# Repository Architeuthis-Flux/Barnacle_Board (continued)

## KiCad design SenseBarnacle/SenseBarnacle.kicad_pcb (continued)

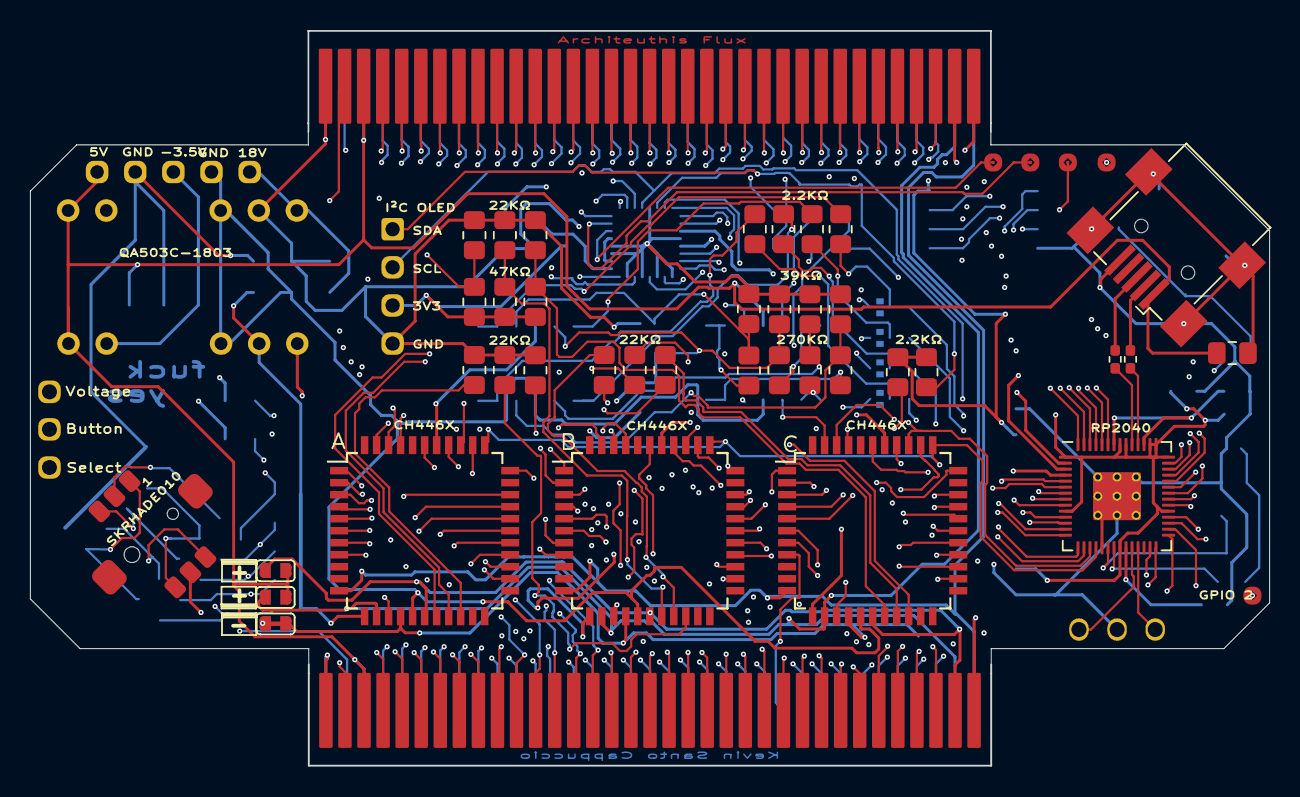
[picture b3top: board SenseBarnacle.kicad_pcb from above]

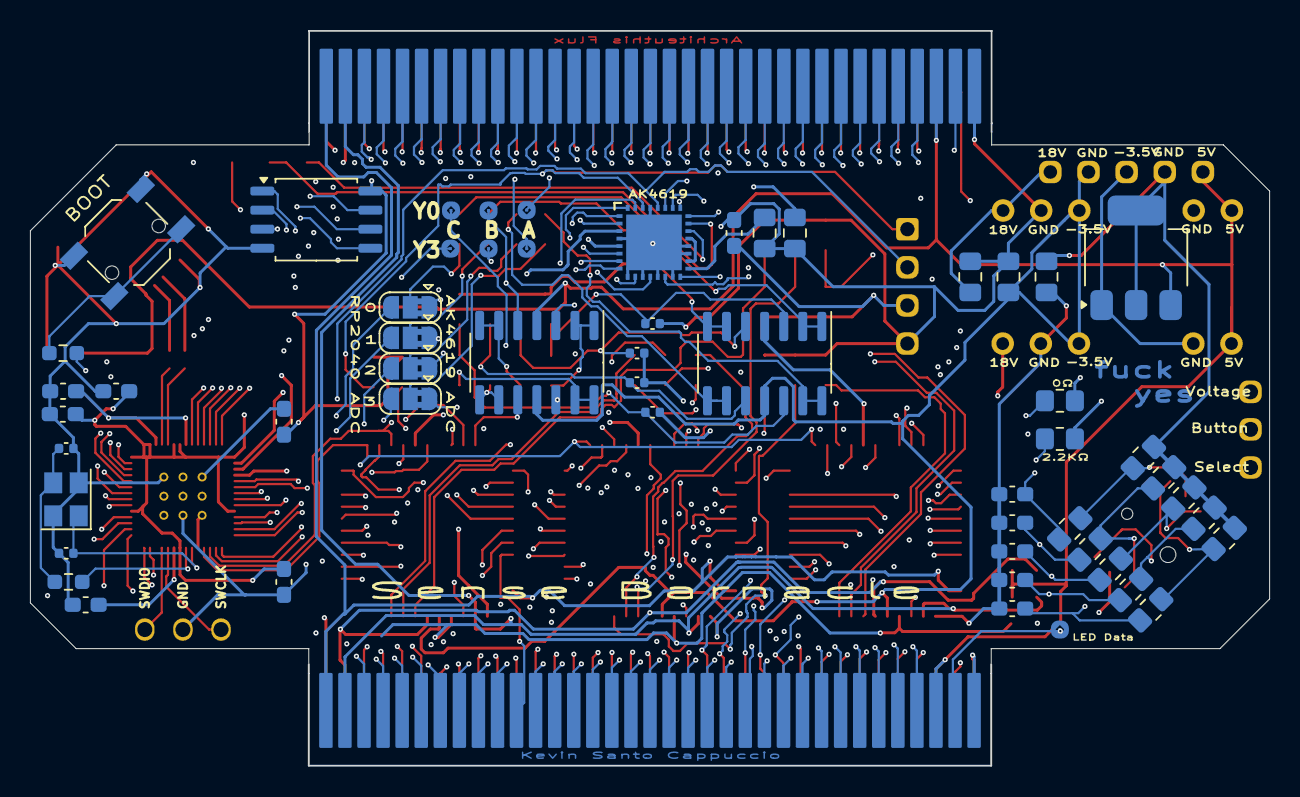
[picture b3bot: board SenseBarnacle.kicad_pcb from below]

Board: 4 copper layers, 82.6 x 48.9 mm, 108 parts (57 on the bottom side), 167 nets.

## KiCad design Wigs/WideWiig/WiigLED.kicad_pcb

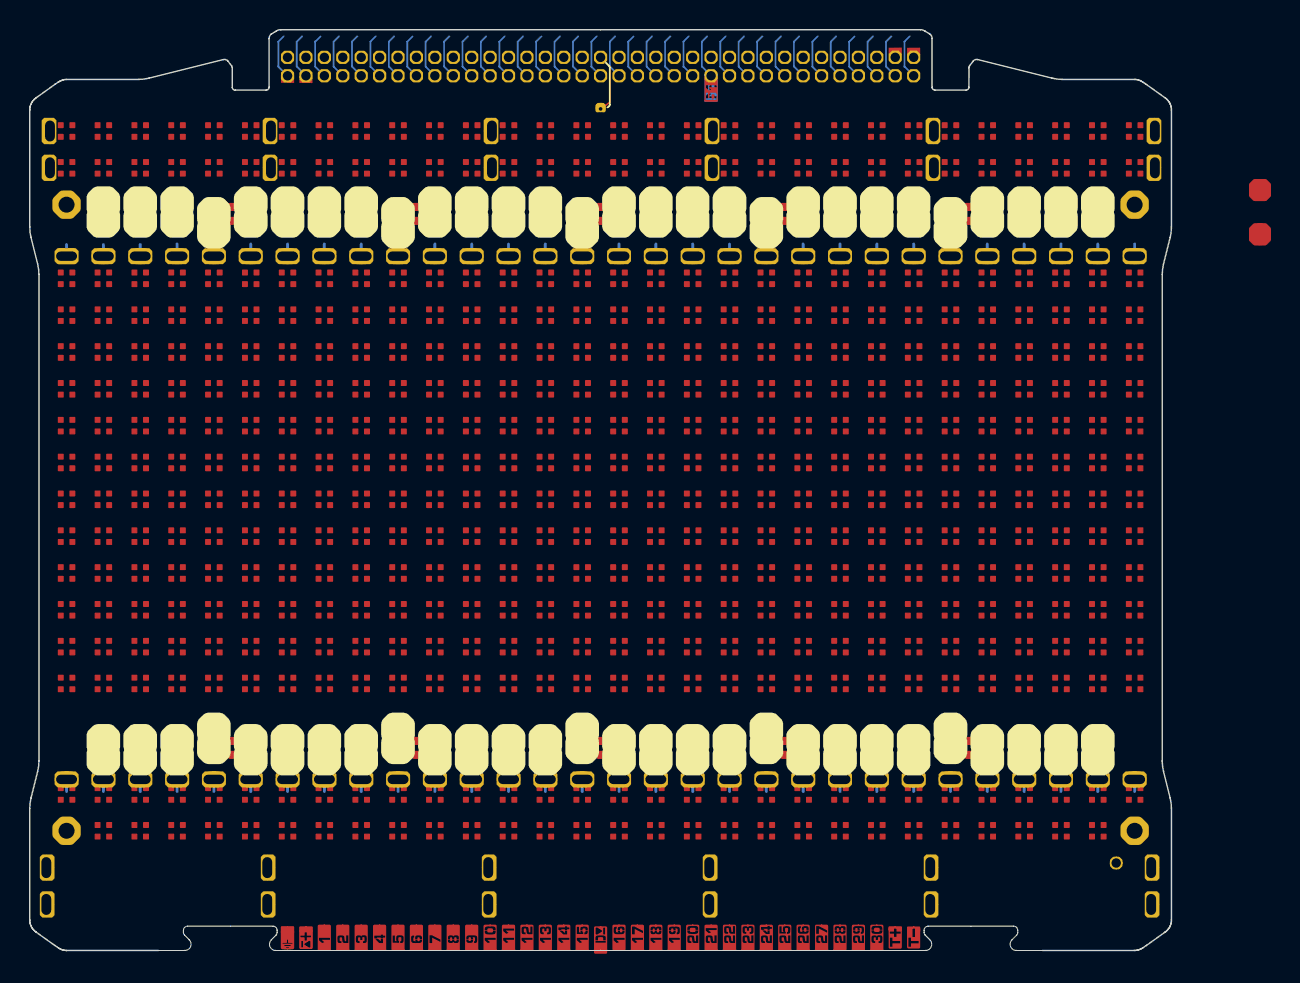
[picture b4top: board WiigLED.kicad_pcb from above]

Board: 4 copper layers, 78.7 x 63.5 mm, 505 parts (0 on the bottom side), 552 nets, no tracks yet.

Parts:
C1, C2, C3, C4, C5, C6, C7, C8, C9, C10, C11, C12, C13, C14: 1uF; C_0402_1005Metric
D11, D12, D13, D14, D15, D16, D21, D22, D23, D24, D25, D26, D31, D32, D33, D34, D35, D36, D41, D42, D43, D44, D45, D46, D51, D52, D53, D54, D55, D56, D61, D62, D63, D64, D65, D66, D71, D72, D73, D74, D75, D76, D81, D82, D83, D84, D85, D86, D91, D92, D93, D94, D95, D96, D101, D102, D103, D104, D105, D106, D111, D112, D113, D114, D115, D116, D121, D122, D123, D124, D125, D126, D131, D132, D133, D134, D135, D136, D141, D142, D143, D144, D145, D146, D151, D152, D153, D154, D155, D156, D161, D162, D163, D164, D165, D166, D171, D172, D173, D174, D175, D176, D181, D182, D183, D184, D185, D186, D191, D192, D193, D194, D195, D196, D201, D202, D203, D204, D205, D206, D211, D212, D213, D214, D215, D216, D221, D222, D223, D224, D225, D226, D231, D232, D233, D234, D235, D236, D241, D242, D243, D244, D245, D246, D251, D252, D253, D254, D255, D256, D261, D262, D263, D264, D265, D266, D271, D272, D273, D274, D275, D276, D281, D282, D283, D284, D285, D286, D291, D292, D293, D294, D295, D296, D301, D302, D303, D304, D305, D306, D311, D312, D313, D314, D315, D316, D321, D322, D323, D324, D325, D326, D331, D332, D333, D334, D335, D336, D341, D342, D343, D344, D345, D346, D351, D352, D353, D354, D355, D356, D361, D362, D363, D364, D365, D366, D371, D372, D373, D374, D375, D376, D381, D382, D383, D384, D385, D386, D391, D392, D393, D394, D395, D396, D401, D402, D403, D404, D405, D406, D411, D412, D413, D414, D415, D416, D421, D422, D423, D424, D425, D426, D431, D432, D433, D434, D435, D436, D441, D442, D443, D444, D445, D446, D451, D452, D453, D454, D455, D456, D461, D462, D463, D464, D465, D466, D471, D472, D473, D474, D475, D476, D481, D482, D483, D484, D485, D486, D491, D492, D493, D494, D495, D496, D501, D502, D503, D504, D505, D506, D511, D512, D513, D514, D515, D516, D521, D522, D523, D524, D525, D526, D531, D532, D533, D534, D535, D536, D541, D542, D543, D544, D545, D546, D551, D552, D553, D554, D555, D556, D561, D562, D563, D564, D565, D566, D571, D572, D573, D574, D575, D576, D581, D582, D583, D584, D585, D586, D591, D592, D593, D594, D595, D596, D601, D602, D603, D604, D605, D606, D611, D612, D613, D614, D615, D616, D617, D618, D619, D621, D622, D623, D624, D625, D626, D627, D628, D629, D631, D632, D633, D634, D635, D636, D637, D638, D639, D641, D642, D643, D644, D645, D646, D647, D648, D649, D6110, D6111, D6112, D6113, D6114, D6115, D6116, D6117, D6118, D6119, D6120, D6121, D6122, D6123, D6124, D6125, D6126, D6127, D6128, D6129, D6130, D6210, D6211, D6212, D6213, D6214, D6215, D6216, D6217, D6218, D6219, D6220, D6221, D6222, D6223, D6224, D6225, D6226, D6227, D6228, D6229, D6230, D6310, D6311, D6312, D6313, D6314, D6315, D6316, D6317, D6318, D6319, D6320, D6321, D6322, D6323, D6324, D6325, D6326, D6327, D6328, D6329, D6330, D6410, D6411, D6412, D6413, D6414, D6415, D6416, D6417, D6418, D6419, D6420, D6421, D6422, D6423, D6424, D6425, D6426, D6427, D6428, D6429, D6430: WS2812B; WS2812B-1313
J1: SENSE_60; Conn_1x1_SenseRiser
J1#2: SENSE_60; HEE70LP03BK_NumberedPads_CardGuide
J2: Barnacle_Connector_70pin; PinHeader_2x35_P1.27_wiig_card
J3: Barnacle_Connector_70pin; SideConnect_sparserrr_Bottom_tighter
J4: SENSE_1; Conn_1x1_SenseRiser
J5: SENSE_30; Conn_1x1_SenseRiser
J6: SENSE_31; Conn_1x1_SenseRiser
J11: Breadboard_6NonHoles
TP1, TP2: GND; TestPoint_Pad_D1.0mm
TP3: LED OUT; PinHeader_1x1_0.6mm_tinyAF

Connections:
+5V: C1.1, C2.1, C3.1, C4.1, C5.1, C6.1, C7.1, C8.1, C9.1, C10.1, C11.1, C12.1, C13.1, C14.1, D11.2 (VDD), D12.2 (VDD), D13.2 (VDD), D14.2 (VDD), D15.2 (VDD), D16.2 (VDD), D21.2 (VDD), D22.2 (VDD), D23.2 (VDD), D24.2 (VDD), D25.2 (VDD), D26.2 (VDD), D31.2 (VDD), D32.2 (VDD), D33.2 (VDD), D34.2 (VDD), D35.2 (VDD), D36.2 (VDD), D41.2 (VDD), D42.2 (VDD), D43.2 (VDD), D44.2 (VDD), D45.2 (VDD), D46.2 (VDD), D51.2 (VDD), D52.2 (VDD), D53.2 (VDD), D54.2 (VDD), D55.2 (VDD), D56.2 (VDD), D61.2 (VDD), D62.2 (VDD), D63.2 (VDD), D64.2 (VDD), D65.2 (VDD), D66.2 (VDD), D71.2 (VDD), D72.2 (VDD), D73.2 (VDD), D74.2 (VDD), D75.2 (VDD), D76.2 (VDD), D81.2 (VDD), D82.2 (VDD), D83.2 (VDD), D84.2 (VDD), D85.2 (VDD), D86.2 (VDD), D91.2 (VDD), D92.2 (VDD), D93.2 (VDD), D94.2 (VDD), D95.2 (VDD), D96.2 (VDD), D101.2 (VDD), D102.2 (VDD), D103.2 (VDD), D104.2 (VDD), D105.2 (VDD), D106.2 (VDD), D111.2 (VDD), D112.2 (VDD), D113.2 (VDD), D114.2 (VDD), D115.2 (VDD), D116.2 (VDD), D121.2 (VDD), D122.2 (VDD), D123.2 (VDD), D124.2 (VDD), D125.2 (VDD), D126.2 (VDD), D131.2 (VDD), D132.2 (VDD), D133.2 (VDD), D134.2 (VDD), D135.2 (VDD), D136.2 (VDD), D141.2 (VDD), D142.2 (VDD), D143.2 (VDD), D144.2 (VDD), D145.2 (VDD), D146.2 (VDD), D151.2 (VDD), D152.2 (VDD), D153.2 (VDD), D154.2 (VDD), D155.2 (VDD), D156.2 (VDD), D161.2 (VDD), D162.2 (VDD), D163.2 (VDD), D164.2 (VDD), D165.2 (VDD), D166.2 (VDD), D171.2 (VDD), D172.2 (VDD), D173.2 (VDD), D174.2 (VDD), D175.2 (VDD), D176.2 (VDD), D181.2 (VDD), D182.2 (VDD), D183.2 (VDD), D184.2 (VDD), D185.2 (VDD), D186.2 (VDD), D191.2 (VDD), D192.2 (VDD), D193.2 (VDD), D194.2 (VDD), D195.2 (VDD), D196.2 (VDD), D201.2 (VDD), D202.2 (VDD), D203.2 (VDD), D204.2 (VDD), D205.2 (VDD), D206.2 (VDD), D211.2 (VDD), D212.2 (VDD), D213.2 (VDD), D214.2 (VDD), D215.2 (VDD), D216.2 (VDD), D221.2 (VDD), D222.2 (VDD), D223.2 (VDD), D224.2 (VDD), D225.2 (VDD), D226.2 (VDD), D231.2 (VDD), D232.2 (VDD), D233.2 (VDD), D234.2 (VDD), D235.2 (VDD), D236.2 (VDD), D241.2 (VDD), D242.2 (VDD), D243.2 (VDD), D244.2 (VDD), D245.2 (VDD), D246.2 (VDD), D251.2 (VDD), D252.2 (VDD), D253.2 (VDD), D254.2 (VDD), D255.2 (VDD), D256.2 (VDD), D261.2 (VDD), D262.2 (VDD), D263.2 (VDD), D264.2 (VDD), D265.2 (VDD), D266.2 (VDD), D271.2 (VDD), D272.2 (VDD), D273.2 (VDD), D274.2 (VDD), D275.2 (VDD), D276.2 (VDD), D281.2 (VDD), D282.2 (VDD), D283.2 (VDD), D284.2 (VDD), D285.2 (VDD), D286.2 (VDD), D291.2 (VDD), D292.2 (VDD), D293.2 (VDD), D294.2 (VDD), D295.2 (VDD), D296.2 (VDD), D301.2 (VDD), D302.2 (VDD), D303.2 (VDD), D304.2 (VDD), D305.2 (VDD), D306.2 (VDD), D311.2 (VDD), D312.2 (VDD), D313.2 (VDD), D314.2 (VDD), D315.2 (VDD), D316.2 (VDD), D321.2 (VDD), D322.2 (VDD), D323.2 (VDD), D324.2 (VDD), D325.2 (VDD), D326.2 (VDD), D331.2 (VDD), D332.2 (VDD), D333.2 (VDD), D334.2 (VDD), D335.2 (VDD), D336.2 (VDD), D341.2 (VDD), D342.2 (VDD), D343.2 (VDD), D344.2 (VDD), D345.2 (VDD), D346.2 (VDD), D351.2 (VDD), D352.2 (VDD), D353.2 (VDD), D354.2 (VDD), D355.2 (VDD), D356.2 (VDD), D361.2 (VDD), D362.2 (VDD), D363.2 (VDD), D364.2 (VDD), D365.2 (VDD), D366.2 (VDD), D371.2 (VDD), D372.2 (VDD), D373.2 (VDD), D374.2 (VDD), D375.2 (VDD), D376.2 (VDD), D381.2 (VDD), D382.2 (VDD), D383.2 (VDD), D384.2 (VDD), D385.2 (VDD), D386.2 (VDD), D391.2 (VDD), D392.2 (VDD), D393.2 (VDD), D394.2 (VDD), D395.2 (VDD), D396.2 (VDD), D401.2 (VDD), D402.2 (VDD), D403.2 (VDD), D404.2 (VDD), D405.2 (VDD), D406.2 (VDD), D411.2 (VDD), D412.2 (VDD), D413.2 (VDD), D414.2 (VDD), D415.2 (VDD), D416.2 (VDD), D421.2 (VDD), D422.2 (VDD), D423.2 (VDD), D424.2 (VDD), D425.2 (VDD), D426.2 (VDD), D431.2 (VDD), D432.2 (VDD), D433.2 (VDD), D434.2 (VDD), D435.2 (VDD), D436.2 (VDD), D441.2 (VDD), D442.2 (VDD), D443.2 (VDD), D444.2 (VDD), D445.2 (VDD), D446.2 (VDD), D451.2 (VDD), D452.2 (VDD), D453.2 (VDD), D454.2 (VDD), D455.2 (VDD), D456.2 (VDD), D461.2 (VDD), D462.2 (VDD), D463.2 (VDD), D464.2 (VDD), D465.2 (VDD), D466.2 (VDD), D471.2 (VDD), D472.2 (VDD), D473.2 (VDD), D474.2 (VDD), D475.2 (VDD), D476.2 (VDD), D481.2 (VDD), D482.2 (VDD), D483.2 (VDD), D484.2 (VDD), D485.2 (VDD), D486.2 (VDD), D491.2 (VDD), D492.2 (VDD), D493.2 (VDD), D494.2 (VDD), D495.2 (VDD), D496.2 (VDD), D501.2 (VDD), D502.2 (VDD), D503.2 (VDD), D504.2 (VDD), D505.2 (VDD), D506.2 (VDD), D511.2 (VDD), D512.2 (VDD), D513.2 (VDD), D514.2 (VDD), D515.2 (VDD), D516.2 (VDD), D521.2 (VDD), D522.2 (VDD), D523.2 (VDD), D524.2 (VDD), D525.2 (VDD), D526.2 (VDD), D531.2 (VDD), D532.2 (VDD), D533.2 (VDD), D534.2 (VDD), D535.2 (VDD), D536.2 (VDD), D541.2 (VDD), D542.2 (VDD), D543.2 (VDD), D544.2 (VDD), D545.2 (VDD), D546.2 (VDD), D551.2 (VDD), D552.2 (VDD), D553.2 (VDD), D554.2 (VDD), D555.2 (VDD), D556.2 (VDD), D561.2 (VDD), D562.2 (VDD), D563.2 (VDD), D564.2 (VDD), D565.2 (VDD), D566.2 (VDD), D571.2 (VDD), D572.2 (VDD), D573.2 (VDD), D574.2 (VDD), D575.2 (VDD), D576.2 (VDD), D581.2 (VDD), D582.2 (VDD), D583.2 (VDD), D584.2 (VDD), D585.2 (VDD), D586.2 (VDD), D591.2 (VDD), D592.2 (VDD), D593.2 (VDD), D594.2 (VDD), D595.2 (VDD), D596.2 (VDD), D601.2 (VDD), D602.2 (VDD), D603.2 (VDD), D604.2 (VDD), D605.2 (VDD), D606.2 (VDD), D611.2 (VDD), D612.2 (VDD), D613.2 (VDD), D614.2 (VDD), D615.2 (VDD), D616.2 (VDD), D617.2 (VDD), D618.2 (VDD), D619.2 (VDD), D621.2 (VDD), D622.2 (VDD), D623.2 (VDD), D624.2 (VDD), D625.2 (VDD), D626.2 (VDD), D627.2 (VDD), D628.2 (VDD), D629.2 (VDD), D631.2 (VDD), D632.2 (VDD), D633.2 (VDD), D634.2 (VDD), D635.2 (VDD), D636.2 (VDD), D637.2 (VDD), D638.2 (VDD), D639.2 (VDD), D641.2 (VDD), D642.2 (VDD), D643.2 (VDD), D644.2 (VDD), D645.2 (VDD), D646.2 (VDD), D647.2 (VDD), D648.2 (VDD), D649.2 (VDD), D6110.2 (VDD), D6111.2 (VDD), D6112.2 (VDD), D6113.2 (VDD), D6114.2 (VDD), D6115.2 (VDD), D6116.2 (VDD), D6117.2 (VDD), D6118.2 (VDD), D6119.2 (VDD), D6120.2 (VDD), D6121.2 (VDD), D6122.2 (VDD), D6123.2 (VDD), D6124.2 (VDD), D6125.2 (VDD), D6126.2 (VDD), D6127.2 (VDD), D6128.2 (VDD), D6129.2 (VDD), D6130.2 (VDD), D6210.2 (VDD), D6211.2 (VDD), D6212.2 (VDD), D6213.2 (VDD), D6214.2 (VDD), D6215.2 (VDD), D6216.2 (VDD), D6217.2 (VDD), D6218.2 (VDD), D6219.2 (VDD), D6220.2 (VDD), D6221.2 (VDD), D6222.2 (VDD), D6223.2 (VDD), D6224.2 (VDD), D6225.2 (VDD), D6226.2 (VDD), D6227.2 (VDD), D6228.2 (VDD), D6229.2 (VDD), D6230.2 (VDD), D6310.2 (VDD), D6311.2 (VDD), D6312.2 (VDD), D6313.2 (VDD), D6314.2 (VDD), D6315.2 (VDD), D6316.2 (VDD), D6317.2 (VDD), D6318.2 (VDD), D6319.2 (VDD), D6320.2 (VDD), D6321.2 (VDD), D6322.2 (VDD), D6323.2 (VDD), D6324.2 (VDD), D6325.2 (VDD), D6326.2 (VDD), D6327.2 (VDD), D6328.2 (VDD), D6329.2 (VDD), D6330.2 (VDD), D6410.2 (VDD), D6411.2 (VDD), D6412.2 (VDD), D6413.2 (VDD), D6414.2 (VDD), D6415.2 (VDD), D6416.2 (VDD), D6417.2 (VDD), D6418.2 (VDD), D6419.2 (VDD), D6420.2 (VDD), D6421.2 (VDD), D6422.2 (VDD), D6423.2 (VDD), D6424.2 (VDD), D6425.2 (VDD), D6426.2 (VDD), D6427.2 (VDD), D6428.2 (VDD), D6429.2 (VDD)
GND: C1.2, C2.2, C3.2, C4.2, C5.2, C6.2, C7.2, C8.2, C9.2, C10.2, C11.2, C12.2, C13.2, C14.2, D11.3 (VSS), D12.3 (VSS), D13.3 (VSS), D14.3 (VSS), D15.3 (VSS), D16.3 (VSS), D21.3 (VSS), D22.3 (VSS), D23.3 (VSS), D24.3 (VSS), D25.3 (VSS), D26.3 (VSS), D31.3 (VSS), D32.3 (VSS), D33.3 (VSS), D34.3 (VSS), D35.3 (VSS), D36.3 (VSS), D41.3 (VSS), D42.3 (VSS), D43.3 (VSS), D44.3 (VSS), D45.3 (VSS), D46.3 (VSS), D51.3 (VSS), D52.3 (VSS), D53.3 (VSS), D54.3 (VSS), D55.3 (VSS), D56.3 (VSS), D61.3 (VSS), D62.3 (VSS), D63.3 (VSS), D64.3 (VSS), D65.3 (VSS), D66.3 (VSS), D71.3 (VSS), D72.3 (VSS), D73.3 (VSS), D74.3 (VSS), D75.3 (VSS), D76.3 (VSS), D81.3 (VSS), D82.3 (VSS), D83.3 (VSS), D84.3 (VSS), D85.3 (VSS), D86.3 (VSS), D91.3 (VSS), D92.3 (VSS), D93.3 (VSS), D94.3 (VSS), D95.3 (VSS), D96.3 (VSS), D101.3 (VSS), D102.3 (VSS), D103.3 (VSS), D104.3 (VSS), D105.3 (VSS), D106.3 (VSS), D111.3 (VSS), D112.3 (VSS), D113.3 (VSS), D114.3 (VSS), D115.3 (VSS), D116.3 (VSS), D121.3 (VSS), D122.3 (VSS), D123.3 (VSS), D124.3 (VSS), D125.3 (VSS), D126.3 (VSS), D131.3 (VSS), D132.3 (VSS), D133.3 (VSS), D134.3 (VSS), D135.3 (VSS), D136.3 (VSS), D141.3 (VSS), D142.3 (VSS), D143.3 (VSS), D144.3 (VSS), D145.3 (VSS), D146.3 (VSS), D151.3 (VSS), D152.3 (VSS), D153.3 (VSS), D154.3 (VSS), D155.3 (VSS), D156.3 (VSS), D161.3 (VSS), D162.3 (VSS), D163.3 (VSS), D164.3 (VSS), D165.3 (VSS), D166.3 (VSS), D171.3 (VSS), D172.3 (VSS), D173.3 (VSS), D174.3 (VSS), D175.3 (VSS), D176.3 (VSS), D181.3 (VSS), D182.3 (VSS), D183.3 (VSS), D184.3 (VSS), D185.3 (VSS), D186.3 (VSS), D191.3 (VSS), D192.3 (VSS), D193.3 (VSS), D194.3 (VSS), D195.3 (VSS), D196.3 (VSS), D201.3 (VSS), D202.3 (VSS), D203.3 (VSS), D204.3 (VSS), D205.3 (VSS), D206.3 (VSS), D211.3 (VSS), D212.3 (VSS), D213.3 (VSS), D214.3 (VSS), D215.3 (VSS), D216.3 (VSS), D221.3 (VSS), D222.3 (VSS), D223.3 (VSS), D224.3 (VSS), D225.3 (VSS), D226.3 (VSS), D231.3 (VSS), D232.3 (VSS), D233.3 (VSS), D234.3 (VSS), D235.3 (VSS), D236.3 (VSS), D241.3 (VSS), D242.3 (VSS), D243.3 (VSS), D244.3 (VSS), D245.3 (VSS), D246.3 (VSS), D251.3 (VSS), D252.3 (VSS), D253.3 (VSS), D254.3 (VSS), D255.3 (VSS), D256.3 (VSS), D261.3 (VSS), D262.3 (VSS), D263.3 (VSS), D264.3 (VSS), D265.3 (VSS), D266.3 (VSS), D271.3 (VSS), D272.3 (VSS), D273.3 (VSS), D274.3 (VSS), D275.3 (VSS), D276.3 (VSS), D281.3 (VSS), D282.3 (VSS), D283.3 (VSS), D284.3 (VSS), D285.3 (VSS), D286.3 (VSS), D291.3 (VSS), D292.3 (VSS), D293.3 (VSS), D294.3 (VSS), D295.3 (VSS), D296.3 (VSS), D301.3 (VSS), D302.3 (VSS), D303.3 (VSS), D304.3 (VSS), D305.3 (VSS), D306.3 (VSS), D311.3 (VSS), D312.3 (VSS), D313.3 (VSS), D314.3 (VSS), D315.3 (VSS), D316.3 (VSS), D321.3 (VSS), D322.3 (VSS), D323.3 (VSS), D324.3 (VSS), D325.3 (VSS), D326.3 (VSS), D331.3 (VSS), D332.3 (VSS), D333.3 (VSS), D334.3 (VSS), D335.3 (VSS), D336.3 (VSS), D341.3 (VSS), D342.3 (VSS), D343.3 (VSS), D344.3 (VSS), D345.3 (VSS), D346.3 (VSS), D351.3 (VSS), D352.3 (VSS), D353.3 (VSS), D354.3 (VSS), D355.3 (VSS), D356.3 (VSS), D361.3 (VSS), D362.3 (VSS), D363.3 (VSS), D364.3 (VSS), D365.3 (VSS), D366.3 (VSS), D371.3 (VSS), D372.3 (VSS), D373.3 (VSS), D374.3 (VSS), D375.3 (VSS), D376.3 (VSS), D381.3 (VSS), D382.3 (VSS), D383.3 (VSS), D384.3 (VSS), D385.3 (VSS), D386.3 (VSS), D391.3 (VSS), D392.3 (VSS), D393.3 (VSS), D394.3 (VSS), D395.3 (VSS), D396.3 (VSS), D401.3 (VSS), D402.3 (VSS), D403.3 (VSS), D404.3 (VSS), D405.3 (VSS), D406.3 (VSS), D411.3 (VSS), D412.3 (VSS), D413.3 (VSS), D414.3 (VSS), D415.3 (VSS), D416.3 (VSS), D421.3 (VSS), D422.3 (VSS), D423.3 (VSS), D424.3 (VSS), D425.3 (VSS), D426.3 (VSS), D431.3 (VSS), D432.3 (VSS), D433.3 (VSS), D434.3 (VSS), D435.3 (VSS), D436.3 (VSS), D441.3 (VSS), D442.3 (VSS), D443.3 (VSS), D444.3 (VSS), D445.3 (VSS), D446.3 (VSS), D451.3 (VSS), D452.3 (VSS), D453.3 (VSS), D454.3 (VSS), D455.3 (VSS), D456.3 (VSS), D461.3 (VSS), D462.3 (VSS), D463.3 (VSS), D464.3 (VSS), D465.3 (VSS), D466.3 (VSS), D471.3 (VSS), D472.3 (VSS), D473.3 (VSS), D474.3 (VSS), D475.3 (VSS), D476.3 (VSS), D481.3 (VSS), D482.3 (VSS), D483.3 (VSS), D484.3 (VSS), D485.3 (VSS), D486.3 (VSS), D491.3 (VSS), D492.3 (VSS), D493.3 (VSS), D494.3 (VSS), D495.3 (VSS), D496.3 (VSS), D501.3 (VSS), D502.3 (VSS), D503.3 (VSS), D504.3 (VSS), D505.3 (VSS), D506.3 (VSS), D511.3 (VSS), D512.3 (VSS), D513.3 (VSS), D514.3 (VSS), D515.3 (VSS), D516.3 (VSS), D521.3 (VSS), D522.3 (VSS), D523.3 (VSS), D524.3 (VSS), D525.3 (VSS), D526.3 (VSS), D531.3 (VSS), D532.3 (VSS), D533.3 (VSS), D534.3 (VSS), D535.3 (VSS), D536.3 (VSS), D541.3 (VSS), D542.3 (VSS), D543.3 (VSS), D544.3 (VSS), D545.3 (VSS), D546.3 (VSS), D551.3 (VSS), D552.3 (VSS), D553.3 (VSS), D554.3 (VSS), D555.3 (VSS), D556.3 (VSS), D561.3 (VSS), D562.3 (VSS), D563.3 (VSS), D564.3 (VSS), D565.3 (VSS), D566.3 (VSS), D571.3 (VSS), D572.3 (VSS), D573.3 (VSS), D574.3 (VSS), D575.3 (VSS), D576.3 (VSS), D581.3 (VSS), D582.3 (VSS), D583.3 (VSS), D584.3 (VSS), D585.3 (VSS), D586.3 (VSS), D591.3 (VSS), D592.3 (VSS), D593.3 (VSS), D594.3 (VSS), D595.3 (VSS), D596.3 (VSS), D601.3 (VSS), D602.3 (VSS), D603.3 (VSS), D604.3 (VSS), D605.3 (VSS), D606.3 (VSS), D611.3 (VSS), D612.3 (VSS), D613.3 (VSS), D614.3 (VSS), D615.3 (VSS), D616.3 (VSS), D617.3 (VSS), D618.3 (VSS), D619.3 (VSS), D621.3 (VSS), D622.3 (VSS), D623.3 (VSS), D624.3 (VSS), D625.3 (VSS), D626.3 (VSS), D627.3 (VSS), D628.3 (VSS), D629.3 (VSS), D631.3 (VSS), D632.3 (VSS), D633.3 (VSS), D634.3 (VSS), D635.3 (VSS), D636.3 (VSS), D637.3 (VSS), D638.3 (VSS), D639.3 (VSS), D641.3 (VSS), D642.3 (VSS), D643.3 (VSS), D644.3 (VSS), D645.3 (VSS), D646.3 (VSS), D647.3 (VSS), D648.3 (VSS), D649.3 (VSS), D6110.3 (VSS), D6111.3 (VSS), D6112.3 (VSS), D6113.3 (VSS), D6114.3 (VSS), D6115.3 (VSS), D6116.3 (VSS), D6117.3 (VSS), D6118.3 (VSS), D6119.3 (VSS), D6120.3 (VSS), D6121.3 (VSS), D6122.3 (VSS), D6123.3 (VSS), D6124.3 (VSS), D6125.3 (VSS), D6126.3 (VSS), D6127.3 (VSS), D6128.3 (VSS), D6129.3 (VSS), D6130.3 (VSS), D6210.3 (VSS), D6211.3 (VSS), D6212.3 (VSS), D6213.3 (VSS), D6214.3 (VSS), D6215.3 (VSS), D6216.3 (VSS), D6217.3 (VSS), D6218.3 (VSS), D6219.3 (VSS), D6220.3 (VSS), D6221.3 (VSS), D6222.3 (VSS), D6223.3 (VSS), D6224.3 (VSS), D6225.3 (VSS), D6226.3 (VSS), D6227.3 (VSS), D6228.3 (VSS), D6229.3 (VSS), D6230.3 (VSS), D6310.3 (VSS), D6311.3 (VSS), D6312.3 (VSS), D6313.3 (VSS), D6314.3 (VSS), D6315.3 (VSS), D6316.3 (VSS), D6317.3 (VSS), D6318.3 (VSS), D6319.3 (VSS), D6320.3 (VSS), D6321.3 (VSS), D6322.3 (VSS), D6323.3 (VSS), D6324.3 (VSS), D6325.3 (VSS), D6326.3 (VSS), D6327.3 (VSS), D6328.3 (VSS), D6329.3 (VSS), D6330.3 (VSS), D6410.3 (VSS), D6411.3 (VSS), D6412.3 (VSS), D6413.3 (VSS), D6414.3 (VSS), D6415.3 (VSS), D6416.3 (VSS), D6417.3 (VSS), D6418.3 (VSS), D6419.3 (VSS), D6420.3 (VSS), D6421.3 (VSS), D6422.3 (VSS), D6423.3 (VSS), D6424.3 (VSS), D6425.3 (VSS), D6426.3 (VSS), D6427.3 (VSS), D6428.3 (VSS), D6429.3 (VSS), D6430.3 (VSS), TP1.1 (1_1), TP2.1 (1_1)
LED_5V: J2.70 (LED_5V), J3.70 (LED_5V)
LED_60_OUT: D606.1 (DOUT), D611.4 (DIN)
LED_DATA_BBin: D11.4 (DIN), J2.68 (LED_DATA_BBin), J3.68 (LED_DATA_BBin)
LED_DATA_BBout: D6430.1 (DOUT), J2.65 (LED_DATA_BBout), J3.65 (LED_DATA_BBout), TP3.1 (1_1)
LED_GND: J2.69 (LED_GND), J3.69 (LED_GND)
unnamed: D11.1 (DOUT), D12.4 (DIN)
unnamed: D12.1 (DOUT), D13.4 (DIN)
unnamed: D13.1 (DOUT), D14.4 (DIN)
unnamed: D14.1 (DOUT), D15.4 (DIN)
unnamed: D15.1 (DOUT), D16.4 (DIN)
unnamed: D16.1 (DOUT), D21.4 (DIN)
unnamed: D21.1 (DOUT), D22.4 (DIN)
unnamed: D22.1 (DOUT), D23.4 (DIN)
unnamed: D23.1 (DOUT), D24.4 (DIN)
unnamed: D24.1 (DOUT), D25.4 (DIN)
unnamed: D25.1 (DOUT), D26.4 (DIN)
unnamed: D26.1 (DOUT), D31.4 (DIN)
unnamed: D31.1 (DOUT), D32.4 (DIN)
unnamed: D32.1 (DOUT), D33.4 (DIN)
unnamed: D33.1 (DOUT), D34.4 (DIN)
unnamed: D34.1 (DOUT), D35.4 (DIN)
unnamed: D35.1 (DOUT), D36.4 (DIN)
unnamed: D36.1 (DOUT), D41.4 (DIN)
unnamed: D41.1 (DOUT), D42.4 (DIN)
unnamed: D42.1 (DOUT), D43.4 (DIN)
unnamed: D43.1 (DOUT), D44.4 (DIN)
unnamed: D44.1 (DOUT), D45.4 (DIN)
unnamed: D45.1 (DOUT), D46.4 (DIN)
unnamed: D46.1 (DOUT), D51.4 (DIN)
unnamed: D51.1 (DOUT), D52.4 (DIN)
unnamed: D52.1 (DOUT), D53.4 (DIN)
unnamed: D53.1 (DOUT), D54.4 (DIN)
unnamed: D54.1 (DOUT), D55.4 (DIN)
unnamed: D55.1 (DOUT), D56.4 (DIN)
unnamed: D56.1 (DOUT), D61.4 (DIN)
unnamed: D61.1 (DOUT), D62.4 (DIN)
unnamed: D62.1 (DOUT), D63.4 (DIN)
unnamed: D63.1 (DOUT), D64.4 (DIN)
unnamed: D64.1 (DOUT), D65.4 (DIN)
unnamed: D65.1 (DOUT), D66.4 (DIN)
unnamed: D66.1 (DOUT), D71.4 (DIN)
unnamed: D71.1 (DOUT), D72.4 (DIN)
unnamed: D72.1 (DOUT), D73.4 (DIN)
unnamed: D73.1 (DOUT), D74.4 (DIN)
unnamed: D74.1 (DOUT), D75.4 (DIN)
unnamed: D75.1 (DOUT), D76.4 (DIN)
unnamed: D76.1 (DOUT), D81.4 (DIN)
unnamed: D81.1 (DOUT), D82.4 (DIN)
unnamed: D82.1 (DOUT), D83.4 (DIN)
unnamed: D83.1 (DOUT), D84.4 (DIN)
unnamed: D84.1 (DOUT), D85.4 (DIN)
unnamed: D85.1 (DOUT), D86.4 (DIN)
unnamed: D86.1 (DOUT), D91.4 (DIN)
unnamed: D91.1 (DOUT), D92.4 (DIN)
unnamed: D92.1 (DOUT), D93.4 (DIN)
unnamed: D93.1 (DOUT), D94.4 (DIN)
unnamed: D94.1 (DOUT), D95.4 (DIN)
unnamed: D95.1 (DOUT), D96.4 (DIN)
unnamed: D96.1 (DOUT), D101.4 (DIN)
unnamed: D101.1 (DOUT), D102.4 (DIN)
unnamed: D102.1 (DOUT), D103.4 (DIN)
unnamed: D103.1 (DOUT), D104.4 (DIN)
unnamed: D104.1 (DOUT), D105.4 (DIN)
unnamed: D105.1 (DOUT), D106.4 (DIN)
unnamed: D106.1 (DOUT), D111.4 (DIN)
unnamed: D111.1 (DOUT), D112.4 (DIN)
unnamed: D112.1 (DOUT), D113.4 (DIN)
unnamed: D113.1 (DOUT), D114.4 (DIN)
unnamed: D114.1 (DOUT), D115.4 (DIN)
unnamed: D115.1 (DOUT), D116.4 (DIN)
unnamed: D116.1 (DOUT), D121.4 (DIN)
unnamed: D121.1 (DOUT), D122.4 (DIN)
unnamed: D122.1 (DOUT), D123.4 (DIN)
unnamed: D123.1 (DOUT), D124.4 (DIN)
unnamed: D124.1 (DOUT), D125.4 (DIN)
unnamed: D125.1 (DOUT), D126.4 (DIN)
unnamed: D126.1 (DOUT), D131.4 (DIN)
unnamed: D131.1 (DOUT), D132.4 (DIN)
unnamed: D132.1 (DOUT), D133.4 (DIN)
unnamed: D133.1 (DOUT), D134.4 (DIN)
unnamed: D134.1 (DOUT), D135.4 (DIN)
unnamed: D135.1 (DOUT), D136.4 (DIN)
unnamed: D136.1 (DOUT), D141.4 (DIN)
unnamed: D141.1 (DOUT), D142.4 (DIN)
unnamed: D142.1 (DOUT), D143.4 (DIN)
unnamed: D143.1 (DOUT), D144.4 (DIN)
unnamed: D144.1 (DOUT), D145.4 (DIN)
unnamed: D145.1 (DOUT), D146.4 (DIN)
unnamed: D146.1 (DOUT), D151.4 (DIN)
unnamed: D151.1 (DOUT), D152.4 (DIN)
unnamed: D152.1 (DOUT), D153.4 (DIN)
unnamed: D153.1 (DOUT), D154.4 (DIN)
unnamed: D154.1 (DOUT), D155.4 (DIN)
unnamed: D155.1 (DOUT), D156.4 (DIN)
unnamed: D156.1 (DOUT), D161.4 (DIN)
unnamed: D161.1 (DOUT), D162.4 (DIN)
unnamed: D162.1 (DOUT), D163.4 (DIN)
unnamed: D163.1 (DOUT), D164.4 (DIN)
unnamed: D164.1 (DOUT), D165.4 (DIN)
unnamed: D165.1 (DOUT), D166.4 (DIN)
unnamed: D166.1 (DOUT), D171.4 (DIN)
unnamed: D171.1 (DOUT), D172.4 (DIN)
unnamed: D172.1 (DOUT), D173.4 (DIN)
unnamed: D173.1 (DOUT), D174.4 (DIN)
unnamed: D174.1 (DOUT), D175.4 (DIN)
unnamed: D175.1 (DOUT), D176.4 (DIN)
unnamed: D176.1 (DOUT), D181.4 (DIN)
unnamed: D181.1 (DOUT), D182.4 (DIN)
unnamed: D182.1 (DOUT), D183.4 (DIN)
unnamed: D183.1 (DOUT), D184.4 (DIN)
unnamed: D184.1 (DOUT), D185.4 (DIN)
unnamed: D185.1 (DOUT), D186.4 (DIN)
unnamed: D186.1 (DOUT), D191.4 (DIN)
unnamed: D191.1 (DOUT), D192.4 (DIN)
unnamed: D192.1 (DOUT), D193.4 (DIN)
unnamed: D193.1 (DOUT), D194.4 (DIN)
unnamed: D194.1 (DOUT), D195.4 (DIN)
unnamed: D195.1 (DOUT), D196.4 (DIN)
unnamed: D196.1 (DOUT), D201.4 (DIN)
unnamed: D201.1 (DOUT), D202.4 (DIN)
unnamed: D202.1 (DOUT), D203.4 (DIN)
unnamed: D203.1 (DOUT), D204.4 (DIN)
unnamed: D204.1 (DOUT), D205.4 (DIN)
unnamed: D205.1 (DOUT), D206.4 (DIN)
unnamed: D206.1 (DOUT), D211.4 (DIN)
unnamed: D211.1 (DOUT), D212.4 (DIN)
unnamed: D212.1 (DOUT), D213.4 (DIN)
unnamed: D213.1 (DOUT), D214.4 (DIN)
unnamed: D214.1 (DOUT), D215.4 (DIN)
unnamed: D215.1 (DOUT), D216.4 (DIN)
unnamed: D216.1 (DOUT), D221.4 (DIN)
unnamed: D221.1 (DOUT), D222.4 (DIN)
unnamed: D222.1 (DOUT), D223.4 (DIN)
unnamed: D223.1 (DOUT), D224.4 (DIN)
unnamed: D224.1 (DOUT), D225.4 (DIN)
unnamed: D225.1 (DOUT), D226.4 (DIN)
unnamed: D226.1 (DOUT), D231.4 (DIN)
unnamed: D231.1 (DOUT), D232.4 (DIN)
unnamed: D232.1 (DOUT), D233.4 (DIN)
unnamed: D233.1 (DOUT), D234.4 (DIN)
unnamed: D234.1 (DOUT), D235.4 (DIN)
unnamed: D235.1 (DOUT), D236.4 (DIN)
unnamed: D236.1 (DOUT), D241.4 (DIN)
unnamed: D241.1 (DOUT), D242.4 (DIN)
unnamed: D242.1 (DOUT), D243.4 (DIN)
unnamed: D243.1 (DOUT), D244.4 (DIN)
unnamed: D244.1 (DOUT), D245.4 (DIN)
unnamed: D245.1 (DOUT), D246.4 (DIN)
unnamed: D246.1 (DOUT), D251.4 (DIN)
unnamed: D251.1 (DOUT), D252.4 (DIN)
unnamed: D252.1 (DOUT), D253.4 (DIN)
unnamed: D253.1 (DOUT), D254.4 (DIN)
unnamed: D254.1 (DOUT), D255.4 (DIN)
unnamed: D255.1 (DOUT), D256.4 (DIN)
unnamed: D256.1 (DOUT), D261.4 (DIN)
unnamed: D261.1 (DOUT), D262.4 (DIN)
unnamed: D262.1 (DOUT), D263.4 (DIN)
unnamed: D263.1 (DOUT), D264.4 (DIN)
unnamed: D264.1 (DOUT), D265.4 (DIN)
unnamed: D265.1 (DOUT), D266.4 (DIN)
unnamed: D266.1 (DOUT), D271.4 (DIN)
unnamed: D271.1 (DOUT), D272.4 (DIN)
unnamed: D272.1 (DOUT), D273.4 (DIN)
unnamed: D273.1 (DOUT), D274.4 (DIN)
unnamed: D274.1 (DOUT), D275.4 (DIN)
unnamed: D275.1 (DOUT), D276.4 (DIN)
unnamed: D276.1 (DOUT), D281.4 (DIN)
unnamed: D281.1 (DOUT), D282.4 (DIN)
unnamed: D282.1 (DOUT), D283.4 (DIN)
unnamed: D283.1 (DOUT), D284.4 (DIN)
unnamed: D284.1 (DOUT), D285.4 (DIN)
unnamed: D285.1 (DOUT), D286.4 (DIN)
unnamed: D286.1 (DOUT), D291.4 (DIN)
unnamed: D291.1 (DOUT), D292.4 (DIN)
unnamed: D292.1 (DOUT), D293.4 (DIN)
unnamed: D293.1 (DOUT), D294.4 (DIN)
unnamed: D294.1 (DOUT), D295.4 (DIN)
unnamed: D295.1 (DOUT), D296.4 (DIN)
unnamed: D296.1 (DOUT), D301.4 (DIN)
unnamed: D301.1 (DOUT), D302.4 (DIN)
unnamed: D302.1 (DOUT), D303.4 (DIN)
unnamed: D303.1 (DOUT), D304.4 (DIN)
unnamed: D304.1 (DOUT), D305.4 (DIN)
unnamed: D305.1 (DOUT), D306.4 (DIN)
unnamed: D306.1 (DOUT), D311.4 (DIN)
unnamed: D311.1 (DOUT), D312.4 (DIN)
unnamed: D312.1 (DOUT), D313.4 (DIN)
unnamed: D313.1 (DOUT), D314.4 (DIN)
unnamed: D314.1 (DOUT), D315.4 (DIN)
unnamed: D315.1 (DOUT), D316.4 (DIN)
unnamed: D316.1 (DOUT), D321.4 (DIN)
unnamed: D321.1 (DOUT), D322.4 (DIN)
unnamed: D322.1 (DOUT), D323.4 (DIN)
unnamed: D323.1 (DOUT), D324.4 (DIN)
unnamed: D324.1 (DOUT), D325.4 (DIN)
unnamed: D325.1 (DOUT), D326.4 (DIN)
unnamed: D326.1 (DOUT), D331.4 (DIN)
unnamed: D331.1 (DOUT), D332.4 (DIN)
unnamed: D332.1 (DOUT), D333.4 (DIN)
unnamed: D333.1 (DOUT), D334.4 (DIN)
unnamed: D334.1 (DOUT), D335.4 (DIN)
unnamed: D335.1 (DOUT), D336.4 (DIN)
unnamed: D336.1 (DOUT), D341.4 (DIN)
unnamed: D341.1 (DOUT), D342.4 (DIN)
unnamed: D342.1 (DOUT), D343.4 (DIN)
unnamed: D343.1 (DOUT), D344.4 (DIN)
unnamed: D344.1 (DOUT), D345.4 (DIN)
unnamed: D345.1 (DOUT), D346.4 (DIN)
unnamed: D346.1 (DOUT), D351.4 (DIN)
unnamed: D351.1 (DOUT), D352.4 (DIN)
unnamed: D352.1 (DOUT), D353.4 (DIN)
unnamed: D353.1 (DOUT), D354.4 (DIN)
unnamed: D354.1 (DOUT), D355.4 (DIN)
unnamed: D355.1 (DOUT), D356.4 (DIN)
unnamed: D356.1 (DOUT), D361.4 (DIN)
unnamed: D361.1 (DOUT), D362.4 (DIN)
unnamed: D362.1 (DOUT), D363.4 (DIN)
unnamed: D363.1 (DOUT), D364.4 (DIN)
unnamed: D364.1 (DOUT), D365.4 (DIN)
unnamed: D365.1 (DOUT), D366.4 (DIN)
unnamed: D366.1 (DOUT), D371.4 (DIN)
unnamed: D371.1 (DOUT), D372.4 (DIN)
unnamed: D372.1 (DOUT), D373.4 (DIN)
unnamed: D373.1 (DOUT), D374.4 (DIN)
unnamed: D374.1 (DOUT), D375.4 (DIN)
unnamed: D375.1 (DOUT), D376.4 (DIN)
unnamed: D376.1 (DOUT), D381.4 (DIN)
unnamed: D381.1 (DOUT), D382.4 (DIN)
unnamed: D382.1 (DOUT), D383.4 (DIN)
unnamed: D383.1 (DOUT), D384.4 (DIN)
unnamed: D384.1 (DOUT), D385.4 (DIN)
unnamed: D385.1 (DOUT), D386.4 (DIN)
unnamed: D386.1 (DOUT), D391.4 (DIN)
unnamed: D391.1 (DOUT), D392.4 (DIN)
unnamed: D392.1 (DOUT), D393.4 (DIN)
unnamed: D393.1 (DOUT), D394.4 (DIN)
unnamed: D394.1 (DOUT), D395.4 (DIN)
unnamed: D395.1 (DOUT), D396.4 (DIN)
unnamed: D396.1 (DOUT), D401.4 (DIN)
unnamed: D401.1 (DOUT), D402.4 (DIN)
unnamed: D402.1 (DOUT), D403.4 (DIN)
unnamed: D403.1 (DOUT), D404.4 (DIN)
unnamed: D404.1 (DOUT), D405.4 (DIN)
unnamed: D405.1 (DOUT), D406.4 (DIN)
unnamed: D406.1 (DOUT), D411.4 (DIN)
unnamed: D411.1 (DOUT), D412.4 (DIN)
unnamed: D412.1 (DOUT), D413.4 (DIN)
unnamed: D413.1 (DOUT), D414.4 (DIN)
unnamed: D414.1 (DOUT), D415.4 (DIN)
unnamed: D415.1 (DOUT), D416.4 (DIN)
unnamed: D416.1 (DOUT), D421.4 (DIN)
unnamed: D421.1 (DOUT), D422.4 (DIN)
unnamed: D422.1 (DOUT), D423.4 (DIN)
unnamed: D423.1 (DOUT), D424.4 (DIN)
unnamed: D424.1 (DOUT), D425.4 (DIN)
unnamed: D425.1 (DOUT), D426.4 (DIN)
unnamed: D426.1 (DOUT), D431.4 (DIN)
unnamed: D431.1 (DOUT), D432.4 (DIN)
unnamed: D432.1 (DOUT), D433.4 (DIN)
unnamed: D433.1 (DOUT), D434.4 (DIN)
unnamed: D434.1 (DOUT), D435.4 (DIN)
unnamed: D435.1 (DOUT), D436.4 (DIN)
unnamed: D436.1 (DOUT), D441.4 (DIN)
unnamed: D441.1 (DOUT), D442.4 (DIN)
unnamed: D442.1 (DOUT), D443.4 (DIN)
unnamed: D443.1 (DOUT), D444.4 (DIN)
unnamed: D444.1 (DOUT), D445.4 (DIN)
unnamed: D445.1 (DOUT), D446.4 (DIN)
unnamed: D446.1 (DOUT), D451.4 (DIN)
unnamed: D451.1 (DOUT), D452.4 (DIN)
unnamed: D452.1 (DOUT), D453.4 (DIN)
unnamed: D453.1 (DOUT), D454.4 (DIN)
unnamed: D454.1 (DOUT), D455.4 (DIN)
unnamed: D455.1 (DOUT), D456.4 (DIN)
unnamed: D456.1 (DOUT), D461.4 (DIN)
unnamed: D461.1 (DOUT), D462.4 (DIN)
unnamed: D462.1 (DOUT), D463.4 (DIN)
unnamed: D463.1 (DOUT), D464.4 (DIN)
unnamed: D464.1 (DOUT), D465.4 (DIN)
unnamed: D465.1 (DOUT), D466.4 (DIN)
unnamed: D466.1 (DOUT), D471.4 (DIN)
unnamed: D471.1 (DOUT), D472.4 (DIN)
unnamed: D472.1 (DOUT), D473.4 (DIN)
unnamed: D473.1 (DOUT), D474.4 (DIN)
unnamed: D474.1 (DOUT), D475.4 (DIN)
unnamed: D475.1 (DOUT), D476.4 (DIN)
unnamed: D476.1 (DOUT), D481.4 (DIN)
unnamed: D481.1 (DOUT), D482.4 (DIN)
unnamed: D482.1 (DOUT), D483.4 (DIN)
unnamed: D483.1 (DOUT), D484.4 (DIN)
unnamed: D484.1 (DOUT), D485.4 (DIN)
unnamed: D485.1 (DOUT), D486.4 (DIN)
unnamed: D486.1 (DOUT), D491.4 (DIN)
unnamed: D491.1 (DOUT), D492.4 (DIN)
unnamed: D492.1 (DOUT), D493.4 (DIN)
unnamed: D493.1 (DOUT), D494.4 (DIN)
unnamed: D494.1 (DOUT), D495.4 (DIN)
unnamed: D495.1 (DOUT), D496.4 (DIN)
unnamed: D496.1 (DOUT), D501.4 (DIN)
unnamed: D501.1 (DOUT), D502.4 (DIN)
unnamed: D502.1 (DOUT), D503.4 (DIN)
unnamed: D503.1 (DOUT), D504.4 (DIN)
unnamed: D504.1 (DOUT), D505.4 (DIN)
unnamed: D505.1 (DOUT), D506.4 (DIN)
unnamed: D506.1 (DOUT), D511.4 (DIN)
unnamed: D511.1 (DOUT), D512.4 (DIN)
unnamed: D512.1 (DOUT), D513.4 (DIN)
unnamed: D513.1 (DOUT), D514.4 (DIN)
unnamed: D514.1 (DOUT), D515.4 (DIN)
unnamed: D515.1 (DOUT), D516.4 (DIN)
unnamed: D516.1 (DOUT), D521.4 (DIN)
unnamed: D521.1 (DOUT), D522.4 (DIN)
unnamed: D522.1 (DOUT), D523.4 (DIN)
unnamed: D523.1 (DOUT), D524.4 (DIN)
unnamed: D524.1 (DOUT), D525.4 (DIN)
unnamed: D525.1 (DOUT), D526.4 (DIN)
unnamed: D526.1 (DOUT), D531.4 (DIN)
unnamed: D531.1 (DOUT), D532.4 (DIN)
unnamed: D532.1 (DOUT), D533.4 (DIN)
unnamed: D533.1 (DOUT), D534.4 (DIN)
unnamed: D534.1 (DOUT), D535.4 (DIN)
unnamed: D535.1 (DOUT), D536.4 (DIN)
unnamed: D536.1 (DOUT), D541.4 (DIN)
unnamed: D541.1 (DOUT), D542.4 (DIN)
unnamed: D542.1 (DOUT), D543.4 (DIN)
unnamed: D543.1 (DOUT), D544.4 (DIN)
unnamed: D544.1 (DOUT), D545.4 (DIN)
unnamed: D545.1 (DOUT), D546.4 (DIN)
unnamed: D546.1 (DOUT), D551.4 (DIN)
unnamed: D551.1 (DOUT), D552.4 (DIN)
unnamed: D552.1 (DOUT), D553.4 (DIN)
unnamed: D553.1 (DOUT), D554.4 (DIN)
unnamed: D554.1 (DOUT), D555.4 (DIN)
unnamed: D555.1 (DOUT), D556.4 (DIN)
unnamed: D556.1 (DOUT), D561.4 (DIN)
unnamed: D561.1 (DOUT), D562.4 (DIN)
unnamed: D562.1 (DOUT), D563.4 (DIN)
unnamed: D563.1 (DOUT), D564.4 (DIN)
unnamed: D564.1 (DOUT), D565.4 (DIN)
unnamed: D565.1 (DOUT), D566.4 (DIN)
unnamed: D566.1 (DOUT), D571.4 (DIN)
unnamed: D571.1 (DOUT), D572.4 (DIN)
unnamed: D572.1 (DOUT), D573.4 (DIN)
unnamed: D573.1 (DOUT), D574.4 (DIN)
unnamed: D574.1 (DOUT), D575.4 (DIN)
unnamed: D575.1 (DOUT), D576.4 (DIN)
unnamed: D576.1 (DOUT), D581.4 (DIN)
unnamed: D581.1 (DOUT), D582.4 (DIN)
unnamed: D582.1 (DOUT), D583.4 (DIN)
unnamed: D583.1 (DOUT), D584.4 (DIN)
unnamed: D584.1 (DOUT), D585.4 (DIN)
unnamed: D585.1 (DOUT), D586.4 (DIN)
unnamed: D586.1 (DOUT), D591.4 (DIN)
unnamed: D591.1 (DOUT), D592.4 (DIN)
unnamed: D592.1 (DOUT), D593.4 (DIN)
unnamed: D593.1 (DOUT), D594.4 (DIN)
unnamed: D594.1 (DOUT), D595.4 (DIN)
unnamed: D595.1 (DOUT), D596.4 (DIN)
unnamed: D596.1 (DOUT), D601.4 (DIN)
unnamed: D601.1 (DOUT), D602.4 (DIN)
unnamed: D602.1 (DOUT), D603.4 (DIN)
unnamed: D603.1 (DOUT), D604.4 (DIN)
unnamed: D604.1 (DOUT), D605.4 (DIN)
unnamed: D605.1 (DOUT), D606.4 (DIN)
unnamed: D611.1 (DOUT), D612.4 (DIN)
unnamed: D612.1 (DOUT), D613.4 (DIN)
unnamed: D613.1 (DOUT), D614.4 (DIN)
unnamed: D614.1 (DOUT), D615.4 (DIN)
unnamed: D615.1 (DOUT), D616.4 (DIN)
unnamed: D616.1 (DOUT), D617.4 (DIN)
unnamed: D617.1 (DOUT), D618.4 (DIN)
unnamed: D618.1 (DOUT), D619.4 (DIN)
unnamed: D621.1 (DOUT), D622.4 (DIN)
unnamed: D622.1 (DOUT), D623.4 (DIN)
unnamed: D623.1 (DOUT), D624.4 (DIN)
unnamed: D624.1 (DOUT), D625.4 (DIN)
unnamed: D625.1 (DOUT), D626.4 (DIN)
unnamed: D626.1 (DOUT), D627.4 (DIN)
unnamed: D627.1 (DOUT), D628.4 (DIN)
unnamed: D628.1 (DOUT), D629.4 (DIN)
unnamed: D631.1 (DOUT), D632.4 (DIN)
unnamed: D632.1 (DOUT), D633.4 (DIN)
unnamed: D633.1 (DOUT), D634.4 (DIN)
unnamed: D634.1 (DOUT), D635.4 (DIN)
unnamed: D635.1 (DOUT), D636.4 (DIN)
unnamed: D636.1 (DOUT), D637.4 (DIN)
unnamed: D637.1 (DOUT), D638.4 (DIN)
unnamed: D638.1 (DOUT), D639.4 (DIN)
unnamed: D641.1 (DOUT), D642.4 (DIN)
unnamed: D642.1 (DOUT), D643.4 (DIN)
unnamed: D643.1 (DOUT), D644.4 (DIN)
unnamed: D644.1 (DOUT), D645.4 (DIN)
unnamed: D645.1 (DOUT), D646.4 (DIN)
unnamed: D646.1 (DOUT), D647.4 (DIN)
unnamed: D647.1 (DOUT), D648.4 (DIN)
unnamed: D648.1 (DOUT), D649.4 (DIN)
unnamed: D619.1 (DOUT), D6110.4 (DIN)
unnamed: D6110.1 (DOUT), D6111.4 (DIN)
unnamed: D6111.1 (DOUT), D6112.4 (DIN)
unnamed: D6112.1 (DOUT), D6113.4 (DIN)
unnamed: D6113.1 (DOUT), D6114.4 (DIN)
unnamed: D6114.1 (DOUT), D6115.4 (DIN)
unnamed: D6115.1 (DOUT), D6116.4 (DIN)
unnamed: D6116.1 (DOUT), D6117.4 (DIN)
unnamed: D6117.1 (DOUT), D6118.4 (DIN)
unnamed: D6118.1 (DOUT), D6119.4 (DIN)
unnamed: D6119.1 (DOUT), D6120.4 (DIN)
unnamed: D6120.1 (DOUT), D6121.4 (DIN)
unnamed: D6121.1 (DOUT), D6122.4 (DIN)
unnamed: D6122.1 (DOUT), D6123.4 (DIN)
unnamed: D6123.1 (DOUT), D6124.4 (DIN)
unnamed: D6124.1 (DOUT), D6125.4 (DIN)
unnamed: D6125.1 (DOUT), D6126.4 (DIN)
unnamed: D6126.1 (DOUT), D6127.4 (DIN)
unnamed: D6127.1 (DOUT), D6128.4 (DIN)
unnamed: D6128.1 (DOUT), D6129.4 (DIN)
unnamed: D6129.1 (DOUT), D6130.4 (DIN)
unnamed: D621.4 (DIN), D6130.1 (DOUT)
unnamed: D629.1 (DOUT), D6210.4 (DIN)
unnamed: D6210.1 (DOUT), D6211.4 (DIN)
unnamed: D6211.1 (DOUT), D6212.4 (DIN)
unnamed: D6212.1 (DOUT), D6213.4 (DIN)
unnamed: D6213.1 (DOUT), D6214.4 (DIN)
unnamed: D6214.1 (DOUT), D6215.4 (DIN)
unnamed: D6215.1 (DOUT), D6216.4 (DIN)
unnamed: D6216.1 (DOUT), D6217.4 (DIN)
unnamed: D6217.1 (DOUT), D6218.4 (DIN)
unnamed: D6218.1 (DOUT), D6219.4 (DIN)
unnamed: D6219.1 (DOUT), D6220.4 (DIN)
unnamed: D6220.1 (DOUT), D6221.4 (DIN)
unnamed: D6221.1 (DOUT), D6222.4 (DIN)
unnamed: D6222.1 (DOUT), D6223.4 (DIN)
unnamed: D6223.1 (DOUT), D6224.4 (DIN)
unnamed: D6224.1 (DOUT), D6225.4 (DIN)
unnamed: D6225.1 (DOUT), D6226.4 (DIN)
unnamed: D6226.1 (DOUT), D6227.4 (DIN)
unnamed: D6227.1 (DOUT), D6228.4 (DIN)
unnamed: D6228.1 (DOUT), D6229.4 (DIN)
unnamed: D6229.1 (DOUT), D6230.4 (DIN)
unnamed: D631.4 (DIN), D6230.1 (DOUT)
unnamed: D639.1 (DOUT), D6310.4 (DIN)
unnamed: D6310.1 (DOUT), D6311.4 (DIN)
unnamed: D6311.1 (DOUT), D6312.4 (DIN)
unnamed: D6312.1 (DOUT), D6313.4 (DIN)
unnamed: D6313.1 (DOUT), D6314.4 (DIN)
unnamed: D6314.1 (DOUT), D6315.4 (DIN)
unnamed: D6315.1 (DOUT), D6316.4 (DIN)
unnamed: D6316.1 (DOUT), D6317.4 (DIN)
unnamed: D6317.1 (DOUT), D6318.4 (DIN)
unnamed: D6318.1 (DOUT), D6319.4 (DIN)
unnamed: D6319.1 (DOUT), D6320.4 (DIN)
unnamed: D6320.1 (DOUT), D6321.4 (DIN)
unnamed: D6321.1 (DOUT), D6322.4 (DIN)
unnamed: D6322.1 (DOUT), D6323.4 (DIN)
unnamed: D6323.1 (DOUT), D6324.4 (DIN)
unnamed: D6324.1 (DOUT), D6325.4 (DIN)
unnamed: D6325.1 (DOUT), D6326.4 (DIN)
unnamed: D6326.1 (DOUT), D6327.4 (DIN)
unnamed: D6327.1 (DOUT), D6328.4 (DIN)
unnamed: D6328.1 (DOUT), D6329.4 (DIN)
unnamed: D6329.1 (DOUT), D6330.4 (DIN)
unnamed: D641.4 (DIN), D6330.1 (DOUT)
unnamed: D649.1 (DOUT), D6410.4 (DIN)
unnamed: D6410.1 (DOUT), D6411.4 (DIN)
unnamed: D6411.1 (DOUT), D6412.4 (DIN)
unnamed: D6412.1 (DOUT), D6413.4 (DIN)
unnamed: D6413.1 (DOUT), D6414.4 (DIN)
unnamed: D6414.1 (DOUT), D6415.4 (DIN)
unnamed: D6415.1 (DOUT), D6416.4 (DIN)
unnamed: D6416.1 (DOUT), D6417.4 (DIN)
unnamed: D6417.1 (DOUT), D6418.4 (DIN)
unnamed: D6418.1 (DOUT), D6419.4 (DIN)
unnamed: D6419.1 (DOUT), D6420.4 (DIN)
unnamed: D6420.1 (DOUT), D6421.4 (DIN)
unnamed: D6421.1 (DOUT), D6422.4 (DIN)
unnamed: D6422.1 (DOUT), D6423.4 (DIN)
unnamed: D6423.1 (DOUT), D6424.4 (DIN)
unnamed: D6424.1 (DOUT), D6425.4 (DIN)
unnamed: D6425.1 (DOUT), D6426.4 (DIN)
unnamed: D6426.1 (DOUT), D6427.4 (DIN)
unnamed: D6427.1 (DOUT), D6428.4 (DIN)
unnamed: D6428.1 (DOUT), D6429.4 (DIN)
unnamed: D6429.1 (DOUT), D6430.4 (DIN)
unnamed: J2.1, J3.1, J11.1
unnamed: J2.2, J3.2, J11.2
unnamed: J2.3, J3.3, J11.3
unnamed: J2.4, J3.4, J11.4
unnamed: J2.5, J3.5, J11.5
unnamed: J2.6, J3.6, J11.6
unnamed: J2.7, J3.7, J11.7
unnamed: J2.8, J3.8, J11.8
unnamed: J2.9, J3.9, J11.9
unnamed: J2.10, J3.10, J11.10
unnamed: J2.11, J3.11, J11.11
unnamed: J2.12, J3.12, J11.12
unnamed: J2.13, J3.13, J11.13
unnamed: J2.14, J3.14, J11.14
unnamed: J2.15, J3.15, J11.15
unnamed: J2.16, J3.16, J11.16
unnamed: J2.17, J3.17, J11.17
unnamed: J2.18, J3.18, J11.18
unnamed: J2.19, J3.19, J11.19
unnamed: J2.20, J3.20, J11.20
unnamed: J2.21, J3.21, J11.21
unnamed: J2.22, J3.22, J11.22
unnamed: J2.23, J3.23, J11.23
unnamed: J2.24, J3.24, J11.24
unnamed: J2.25, J3.25, J11.25
unnamed: J2.26, J3.26, J11.26
unnamed: J2.27, J3.27, J11.27
unnamed: J2.28, J3.28, J11.28
unnamed: J2.33, J3.33, J11.33 (Pin_1)
unnamed: J2.34, J3.34, J11.34 (Pin_2)
unnamed: J2.35, J3.35, J11.35 (Pin_3)
unnamed: J2.36, J3.36, J11.36 (Pin_4)
unnamed: J2.37, J3.37, J11.37 (Pin_5)
unnamed: J2.38, J3.38, J11.38 (Pin_6)
unnamed: J2.39, J3.39, J11.39 (Pin_7)
unnamed: J2.40, J3.40, J11.40 (Pin_8)
unnamed: J2.41, J3.41, J11.41 (Pin_9)
unnamed: J2.42, J3.42, J11.42 (Pin_10)
unnamed: J2.43, J3.43, J11.43 (Pin_11)
unnamed: J2.44, J3.44, J11.44 (Pin_12)
unnamed: J2.45, J3.45, J11.45 (Pin_13)
unnamed: J2.46, J3.46, J11.46 (Pin_14)
unnamed: J2.47, J3.47, J11.47 (Pin_15)
unnamed: J2.48, J3.48, J11.48 (Pin_16)
unnamed: J2.49, J3.49, J11.49 (Pin_17)
unnamed: J2.50, J3.50, J11.50 (Pin_18)
unnamed: J2.51, J3.51, J11.51 (Pin_19)
unnamed: J2.52, J3.52, J11.52 (Pin_20)
unnamed: J2.53, J3.53, J11.53 (Pin_21)
unnamed: J2.54, J3.54, J11.54 (Pin_22)
unnamed: J2.55, J3.55, J11.55 (Pin_23)
unnamed: J2.56, J3.56, J11.56 (Pin_24)
unnamed: J2.57, J3.57, J11.57 (Pin_25)
unnamed: J2.58, J3.58, J11.58 (Pin_26)
unnamed: J2.59, J3.59, J11.59 (Pin_27)
unnamed: J2.60, J3.60, J11.60 (Pin_28)
unnamed: J5.1 (Pin_1_1), J6.1 (Pin_1_1)
unnamed: J2.64 (B-), J3.64 (B-), J11.64 (Bot_Neg)
unnamed: J2.63 (B+), J3.63 (B+), J11.63 (Bot_Pos)
unnamed: J2.32, J3.32, J11.32 (Pin_0)
unnamed: J2.29, J3.29, J11.29
unnamed: J2.30, J3.30, J11.30
unnamed: J2.31, J3.31, J11.31
unnamed: J2.62 (T-), J3.62 (T-), J11.62 (Top_Neg)
unnamed: J2.61 (T+), J3.61 (T+), J11.61 (Top_Pos)
SENSE_1: J2.67 (SENSE_1), J3.67 (SENSE_1), J4.1 (Pin_1_1)
SENSE_60: J1.1 (Pin_1_1), J2.66 (SENSE_60), J3.66 (SENSE_60)
